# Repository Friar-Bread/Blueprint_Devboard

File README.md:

# Blueprint_Devboard
This is my custom RP2040 devboard I made while following the Hackclub tutorial.
Below you can see the PCBA image of the circuit.

I had a lot of fun creating the schematic and routing the PCB for this project.
I went with a funny alien theme because I like the art style and it was easy for me to do.

----------------

Here is the Schematic:

----------------

And here is the PCB:

----------------

And these are some renders from KiCAD:

----------------

BOM:
| Name                   | Quantity      | Price  | Link                                                                                                                                                                                                                                                                                                                                                                                                                                                                                                                                                                                                                                                                                                                                                                                                                                              |
| ---------------------- | ------------- | ------ | ------------------------------------------------------------------------------------------------------------------------------------------------------------------------------------------------------------------------------------------------------------------------------------------------------------------------------------------------------------------------------------------------------------------------------------------------------------------------------------------------------------------------------------------------------------------------------------------------------------------------------------------------------------------------------------------------------------------------------------------------------------------------------------------------------------------------------------------------- |
| PCBA                   | 5 pcb, 2 pcba | $42    | JLCPCB                                                                                                                                                                                                                                                                                                                                                                                                                                                                                                                                                                                                                                                                                                                                                                                                                                            |
| 1x20 Headers           | 10            | $1.52  | [Link](https://www.aliexpress.com/item/2255800801798474.html?spm=a2g0o.cart.0.0.138e38daeAKDGx&mp=1&pdp_npi=5%40dis%21USD%21USD%201.52%21USD%201.52%21%21USD%201.52%21%21%21%40210319b017663802875661460e623e%2110000013202368859%21ct%21US%216930286785%21%211%210&_gl=1*ytrae6*_gcl_au*MTY4MjYwMzQyNC4xNzY0NTI0NjEx*_ga*MTMyOTc2NTkwNC4xNzY2Mzc2MTI3*_ga_VED1YSGNC7*czE3NjYzODAyNDQkbzIkZzEkdDE3NjYzODAyOTEkajEzJGwwJGgw) |
| 1x3 Headers            | 50            | $1.52  | [Link](https://www.aliexpress.com/item/2255800801798474.html?spm=a2g0o.cart.0.0.138e38daeAKDGx&mp=1&pdp_npi=5%40dis%21USD%21USD%201.52%21USD%201.52%21%21USD%201.52%21%21%21%40210319b017663802875661460e623e%2110000013202368849%21ct%21US%216930286785%21%211%210&_gl=1*ytrae6*_gcl_au*MTY4MjYwMzQyNC4xNzY0NTI0NjEx*_ga*MTMyOTc2NTkwNC4xNzY2Mzc2MTI3*_ga_VED1YSGNC7*czE3NjYzODAyNDQkbzIkZzEkdDE3NjYzODAyOTEkajEzJGwwJGgw) |
| Alixpress tax and fees |               | $0.23  |                                                                                                                                                                                                                                                                                                                                                                                                                                                                                                                                                                                                                                                                                                                                                                                                                                                   |
| Total:                 |               | $45.49 |                                                                                                                                                                                                                                                                                                                                                                                                                                                                                                                                                                                                                                                                                                                                                                                                                                                   |

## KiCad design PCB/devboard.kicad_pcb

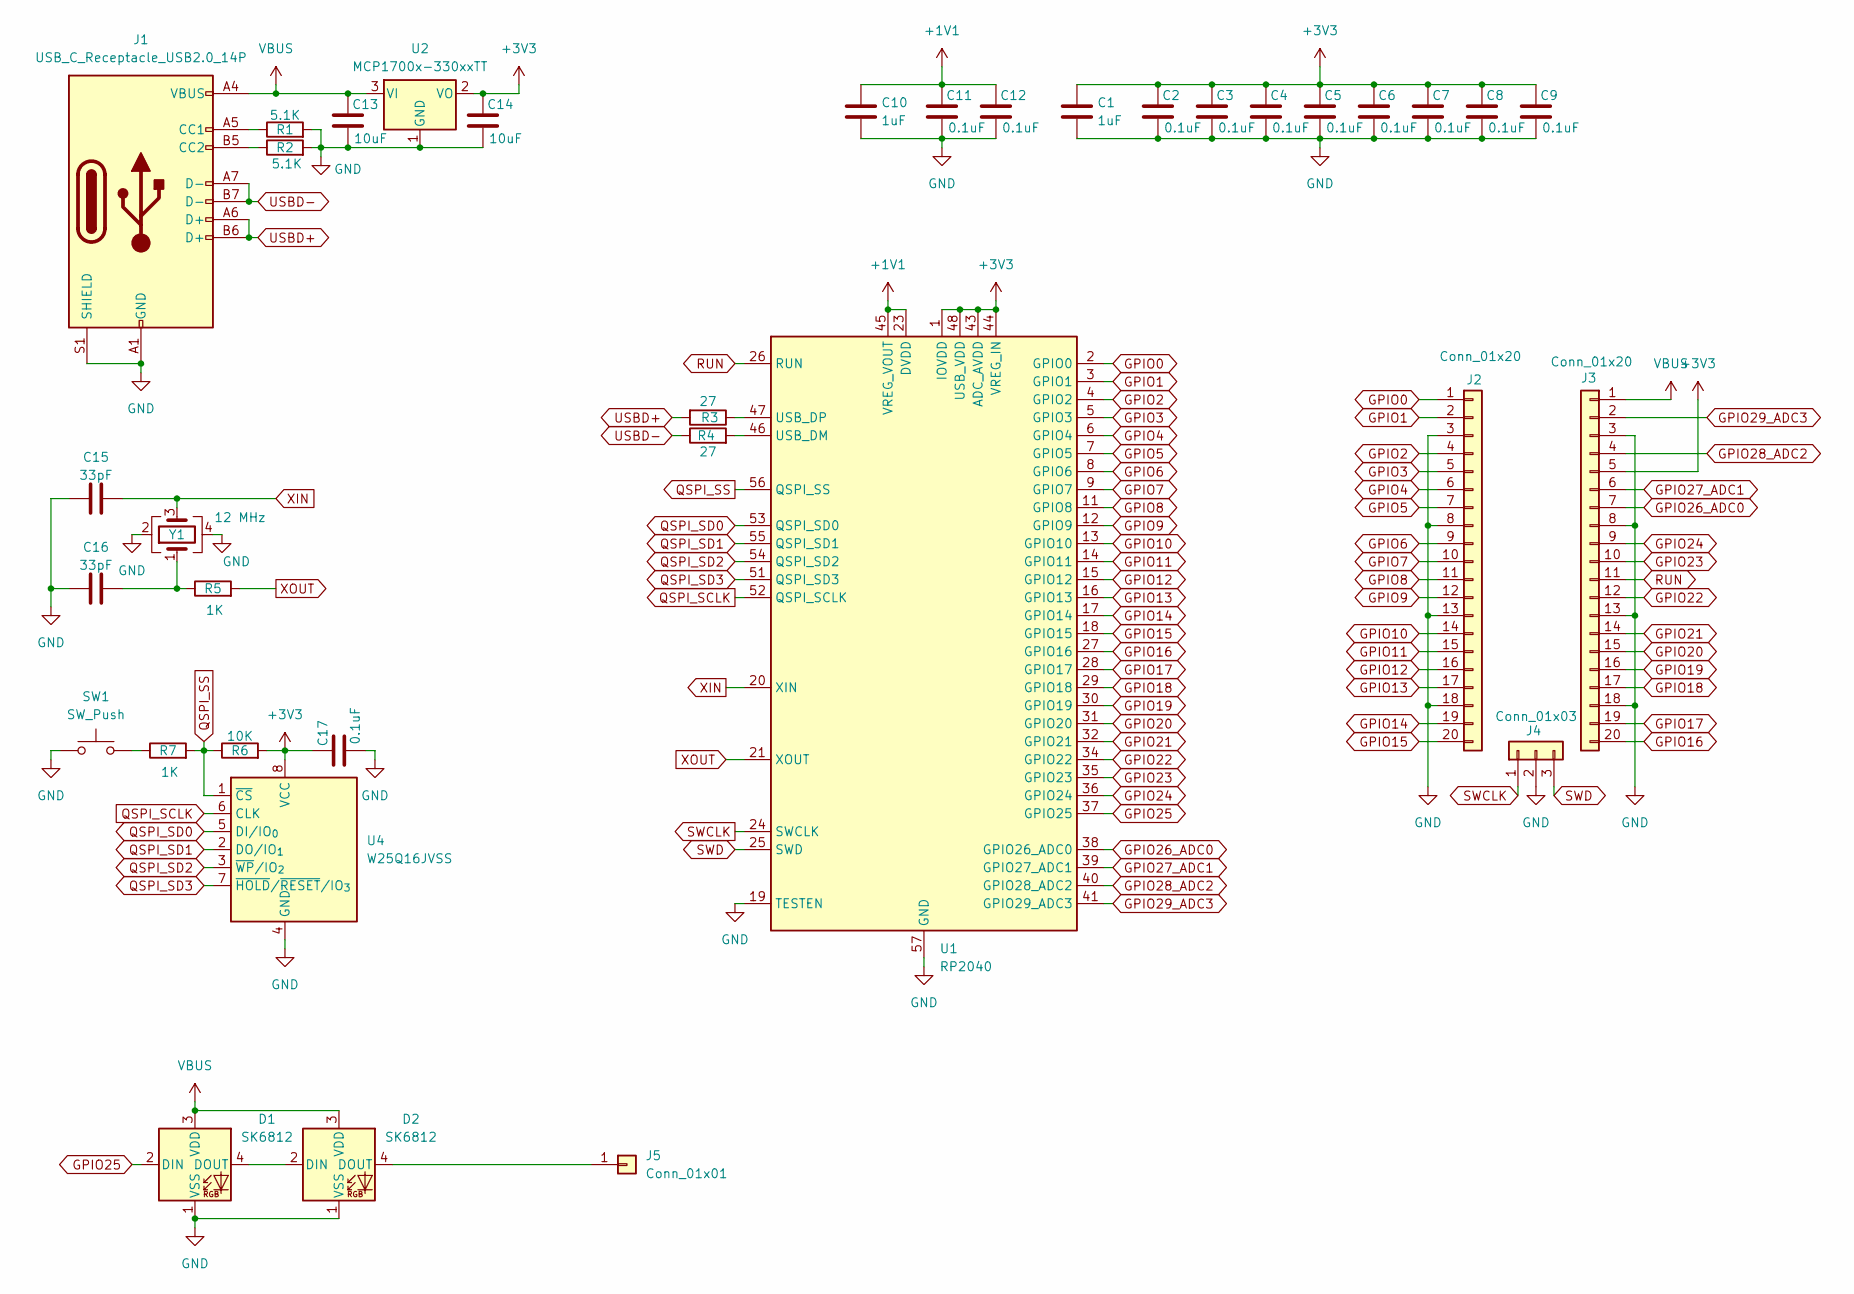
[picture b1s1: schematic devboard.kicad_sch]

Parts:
C1, C10: 1uF; C_0402_1005Metric
C2, C3, C4, C5, C6, C7, C8, C9, C11, C12, C17: 0.1uF; C_0402_1005Metric
C13, C14: 10uF; C_0201_0603Metric
C15, C16: 33pF; C_0402_1005Metric
D1, D2: SK6812; LED_SK6812_PLCC4_5.0x5.0mm_P3.2mm
J1: USB_C_Receptacle_USB2.0_14P; USB_C_Receptacle_HRO_TYPE-C-31-M-12
J2, J3: Conn_01x20; PinHeader_1x20_P2.54mm_Vertical
J4: Conn_01x03; PinHeader_1x03_P2.54mm_Vertical
J5: Conn_01x01; PinHeader_1x01_P2.54mm_Vertical
R1, R2: 5.1K; R_0402_1005Metric
R3, R4: 27; R_0402_1005Metric
R5, R7: 1K; R_0402_1005Metric
R6: 10K; R_0402_1005Metric
SW1: SW_Push; SW_Push_SPST_NO_Alps_SKRK
U1: RP2040; QFN-56-1EP_7x7mm_P0.4mm_EP3.2x3.2mm
U2: MCP1700x-330xxTT; SOT-23
U4: W25Q16JVSS; Winbond_USON-8-1EP_3x2mm_P0.5mm_EP0.2x1.6mm
Y1: 12 MHz; Crystal_SMD_3225-4Pin_3.2x2.5mm

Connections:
+1V1: C10.1, C11.1, C12.1, U1.23 (DVDD), U1.45 (VREG_VOUT), U1.50 (DVDD)
+3V3: C1.1, C2.1, C3.1, C4.1, C5.1, C6.1, C7.1, C8.1, C9.1, C14.1, C17.1, J3.5, R6.2, U1.1 (IOVDD), U1.10 (IOVDD), U1.22 (IOVDD), U1.33 (IOVDD), U1.42 (IOVDD), U1.43 (ADC_AVDD), U1.44 (VREG_IN), U1.48 (USB_VDD), U1.49 (IOVDD), U2.2 (VO), U4.8 (VCC)
GND: C1.2, C2.2, C3.2, C4.2, C5.2, C6.2, C7.2, C8.2, C9.2, C10.2, C11.2, C12.2, C13.2, C14.2, C15.1, C16.1, C17.2, D1.1 (VSS), D2.1 (VSS), J1.A1 (GND), J1.A12 (GND), J1.B1 (GND), J1.B12 (GND), J1.S1 (SHIELD), J2.3, J2.8, J2.13, J2.18, J3.3, J3.8, J3.13, J3.18, J4.2, R1.2, R2.2, SW1.1, U1.19 (TESTEN), U1.57 (GND), U2.1 (GND), U4.4 (GND), Y1.2, Y1.4
GPIO0: J2.1, U1.2 (GPIO0)
GPIO1: J2.2, U1.3 (GPIO1)
GPIO2: J2.4, U1.4 (GPIO2)
GPIO3: J2.5, U1.5 (GPIO3)
GPIO4: J2.6, U1.6 (GPIO4)
GPIO5: J2.7, U1.7 (GPIO5)
GPIO6: J2.9, U1.8 (GPIO6)
GPIO7: J2.10, U1.9 (GPIO7)
GPIO8: J2.11, U1.11 (GPIO8)
GPIO9: J2.12, U1.12 (GPIO9)
GPIO10: J2.14, U1.13 (GPIO10)
GPIO11: J2.15, U1.14 (GPIO11)
GPIO12: J2.16, U1.15 (GPIO12)
GPIO13: J2.17, U1.16 (GPIO13)
GPIO14: J2.19, U1.17 (GPIO14)
GPIO15: J2.20, U1.18 (GPIO15)
GPIO16: J3.20, U1.27 (GPIO16)
GPIO17: J3.19, U1.28 (GPIO17)
GPIO18: J3.17, U1.29 (GPIO18)
GPIO19: J3.16, U1.30 (GPIO19)
GPIO20: J3.15, U1.31 (GPIO20)
GPIO21: J3.14, U1.32 (GPIO21)
GPIO22: J3.12, U1.34 (GPIO22)
GPIO23: J3.10, U1.35 (GPIO23)
GPIO24: J3.9, U1.36 (GPIO24)
GPIO25: D1.2 (DIN), U1.37 (GPIO25)
GPIO26_ADC0: J3.7, U1.38 (GPIO26_ADC0)
GPIO27_ADC1: J3.6, U1.39 (GPIO27_ADC1)
GPIO28_ADC2: J3.4, U1.40 (GPIO28_ADC2)
GPIO29_ADC3: J3.2, U1.41 (GPIO29_ADC3)
unnamed: C16.2, R5.1, Y1.1
unnamed: D1.4 (DOUT), D2.2 (DIN)
unnamed: D2.4 (DOUT), J5.1
unnamed: J1.A5 (CC1), R1.1
unnamed: J1.B5 (CC2), R2.1
unnamed: R7.1, SW1.2
unnamed: R4.2, U1.46 (USB_DM)
unnamed: R3.1, U1.47 (USB_DP)
QSPI_SCLK: U1.52 (QSPI_SCLK), U4.6 (CLK)
QSPI_SD0: U1.53 (QSPI_SD0), U4.5 (DI/IO_{0})
QSPI_SD1: U1.55 (QSPI_SD1), U4.2 (DO/IO_{1})
QSPI_SD2: U1.54 (QSPI_SD2), U4.3 (~WP/IO_{2})
QSPI_SD3: U1.51 (QSPI_SD3), U4.7 (~HOLD/~RESET/IO_{3})
QSPI_SS: R6.1, R7.2, U1.56 (QSPI_SS), U4.1 (~CS)
RUN: J3.11, U1.26 (RUN)
SWCLK: J4.1, U1.24 (SWCLK)
SWD: J4.3, U1.25 (SWD)
USBD+: J1.A6 (D+), J1.B6 (D+), R3.2
USBD-: J1.A7 (D-), J1.B7 (D-), R4.1
VBUS: C13.1, D1.3 (VDD), D2.3 (VDD), J1.A4 (VBUS), J1.A9 (VBUS), J1.B4 (VBUS), J1.B9 (VBUS), J3.1, U2.3 (VI)
XIN: C15.2, U1.20 (XIN), Y1.3
XOUT: R5.2, U1.21 (XOUT)

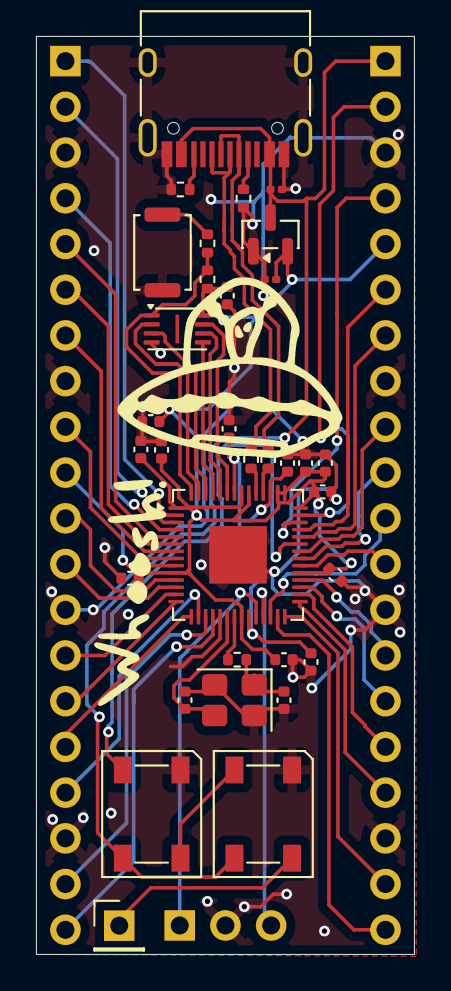
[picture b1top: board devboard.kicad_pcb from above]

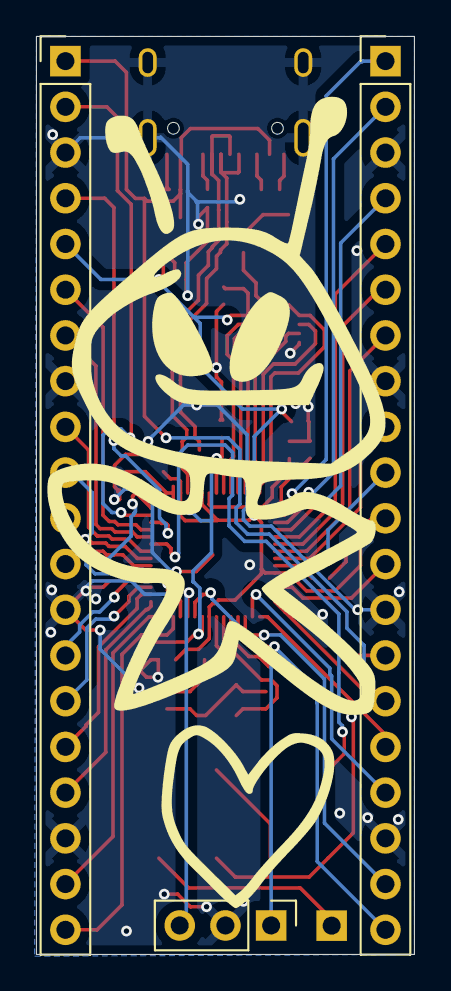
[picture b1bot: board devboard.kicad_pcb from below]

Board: 2 copper layers, 21.0 x 51.0 mm, 36 parts (3 on the bottom side), 55 nets.

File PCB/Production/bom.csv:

Designator,Footprint,Quantity,Value,LCSC Part #
"C1, C10",0402,2,1uF,
"C11, C12, C17, C2, C3, C4, C5, C6, C7, C8, C9",0402,11,0.1uF,
"C13, C14",0201,2,10uF,
"C15, C16",0402,2,33pF,
"D1, D2",LED_SK6812_PLCC4_5.0x5.0mm_P3.2mm,2,SK6812,
J1,USB_C_Receptacle_HRO_TYPE-C-31-M-12,1,USB_C_Receptacle_USB2.0_14P,
"J2, J3",PinHeader_1x20_P2.54mm_Vertical,2,Conn_01x20,
J4,PinHeader_1x03_P2.54mm_Vertical,1,Conn_01x03,
J5,PinHeader_1x01_P2.54mm_Vertical,1,Conn_01x01,
"R1, R2",0402,2,5.1K,
"R3, R4",0402,2,27,
"R5, R7",0402,2,1K,
R6,0402,1,10K,
SW1,SW_Push_SPST_NO_Alps_SKRK,1,SW_Push,
U1,QFN-56-1EP_7x7mm_P0.4mm_EP3.2x3.2mm,1,RP2040,
U2,SOT-23,1,MCP1700x-330xxTT,
U4,Winbond_USON-8-1EP_3x2mm_P0.5mm_EP0.2x1.6mm,1,W25Q16JVSS,
Y1,Crystal_SMD_3225-4Pin_3.2x2.5mm,1,12 MHz,

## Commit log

2025-12-24 added BOM
